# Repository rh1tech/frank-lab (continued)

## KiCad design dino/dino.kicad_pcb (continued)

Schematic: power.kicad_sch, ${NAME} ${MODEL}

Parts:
C41: 1u; C_0603_1608Metric
C42: 680u; CP_Radial_D8.0mm_P3.50mm
C43, C48: 10u; C_0603_1608Metric
C44, C46, C47: 100n; C_0603_1608Metric
C45: 150p; C_0603_1608Metric
C49: 220u; CP_Radial_D6.3mm_P2.50mm
D4: SS34; D_SMA
F1: 1.5A 24V; Fuse_1812_4532Metric
J8: DC-005-5A-2.0; BarrelJack_DC-005; PARTREV A0
JP2: Force On; SolderJumper-2_P1.3mm_Open_Pad1.0x1.5mm
L2: 22uH; Inductor_CDRH104RNP
Q2, Q3: AO3401A; SOT-23-3L_AOS
R33, R34, R35, R37, R39, R40: 100K; R_0603_1608Metric
R36: 10K; R_0603_1608Metric
R38: 39K; R_0603_1608Metric
R41: 8.2K; R_0603_1608Metric
R42: 43K; R_0603_1608Metric
S5: SK12D07VG3NS; Switch_Slide_SK12D07VG3NS
TP2: +5V_DC; TestPoint_Pad_1.0x1.0mm
TP3: +5V_SEL; TestPoint_Pad_1.0x1.0mm
U12: MP1584EN-LF-Z; SOIC-9_P1.27mm; Mouser Part Number 946-MP1584ENLFZ

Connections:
+5V_DC: C47.2, C48.1, C49.1, L2.2, R42.1, TP2.1 (1_1); also elsewhere on the board
+5V_SEL: C41.1, Q3.2 (S), R33.1, TP3.1 (1_1); also elsewhere on the board
GND: C42.2, C43.2, C44.2, C47.1, C48.2, C49.2, D4.2 (A), J8.2, JP2.1 (A), R34.2, R38.2, R39.2, R40.2, R41.1, S5.2, U12.5 (GND), U12.9 (EP); also elsewhere on the board
unnamed: C45.2, R39.1
unnamed: C46.2, D4.1 (K), L2.1, U12.1 (SW)
unnamed: F1.1, J8.1
unnamed: JP2.2 (B), R36.2, S5.3
unnamed: F1.2, Q2.3 (D)
unnamed: Q2.1 (G), R34.1, R35.1
unnamed: C42.1, C43.1, C44.1, Q2.2 (S), R35.2, R37.2, U12.7 (VIN)
unnamed: C41.2, Q3.1 (G), R33.2, R36.1
unnamed: C46.1, U12.8 (BST)
unnamed: C45.1, U12.3 (COMP)
unnamed: R37.1, R38.1, U12.2 (EN)
unnamed: R41.2, R42.2, U12.4 (FB)
unnamed: R40.1, U12.6 (FREQ)
VBUS: Q3.3 (D); also elsewhere on the board

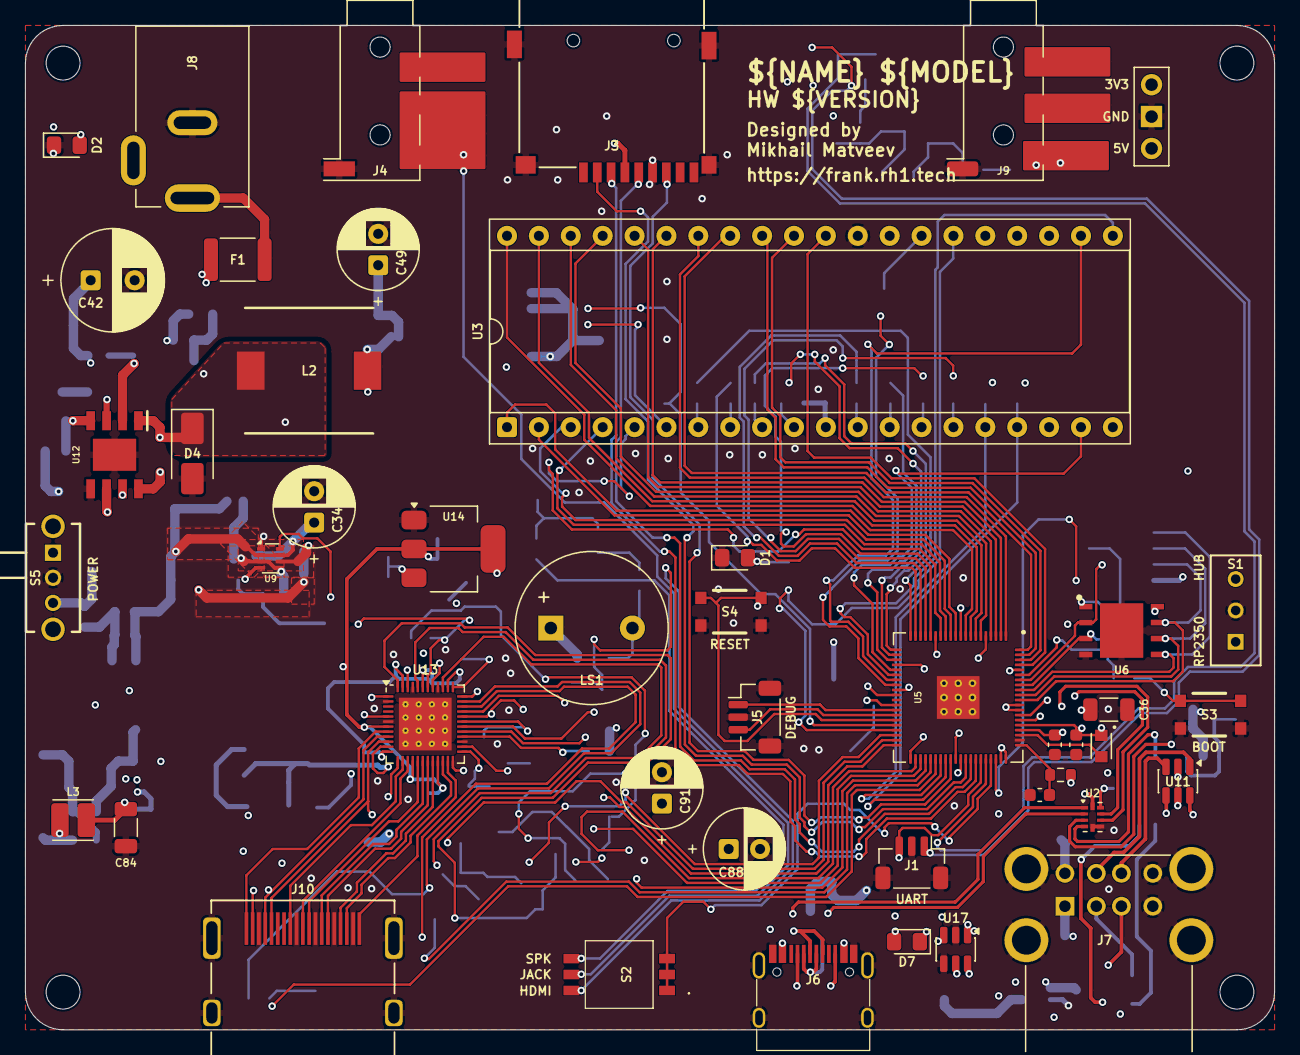
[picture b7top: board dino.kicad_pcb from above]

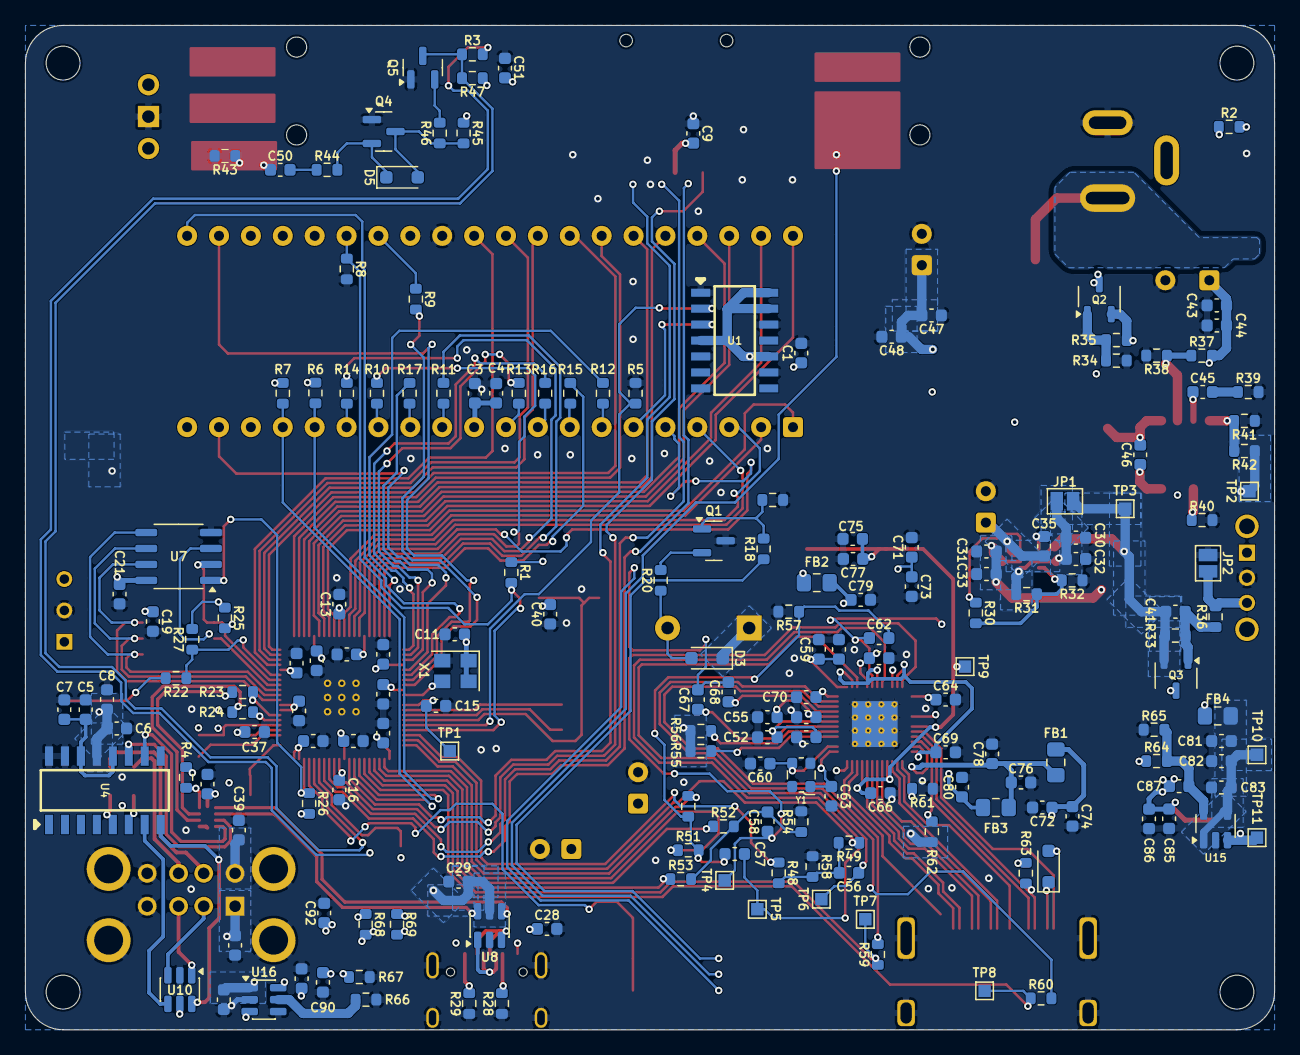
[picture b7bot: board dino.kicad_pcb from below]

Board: 4 copper layers, 99.5 x 80.0 mm, 234 parts (185 on the bottom side), 174 nets.

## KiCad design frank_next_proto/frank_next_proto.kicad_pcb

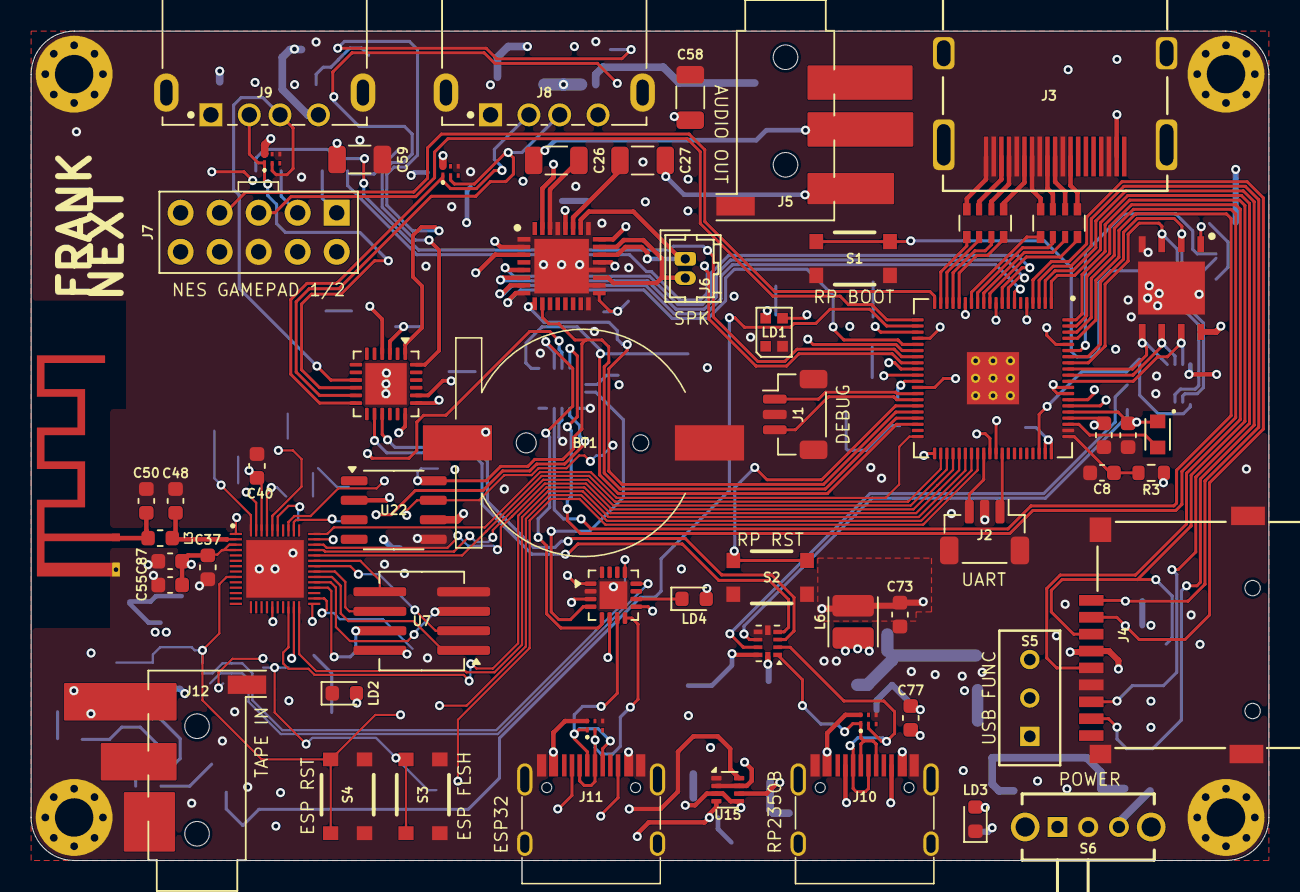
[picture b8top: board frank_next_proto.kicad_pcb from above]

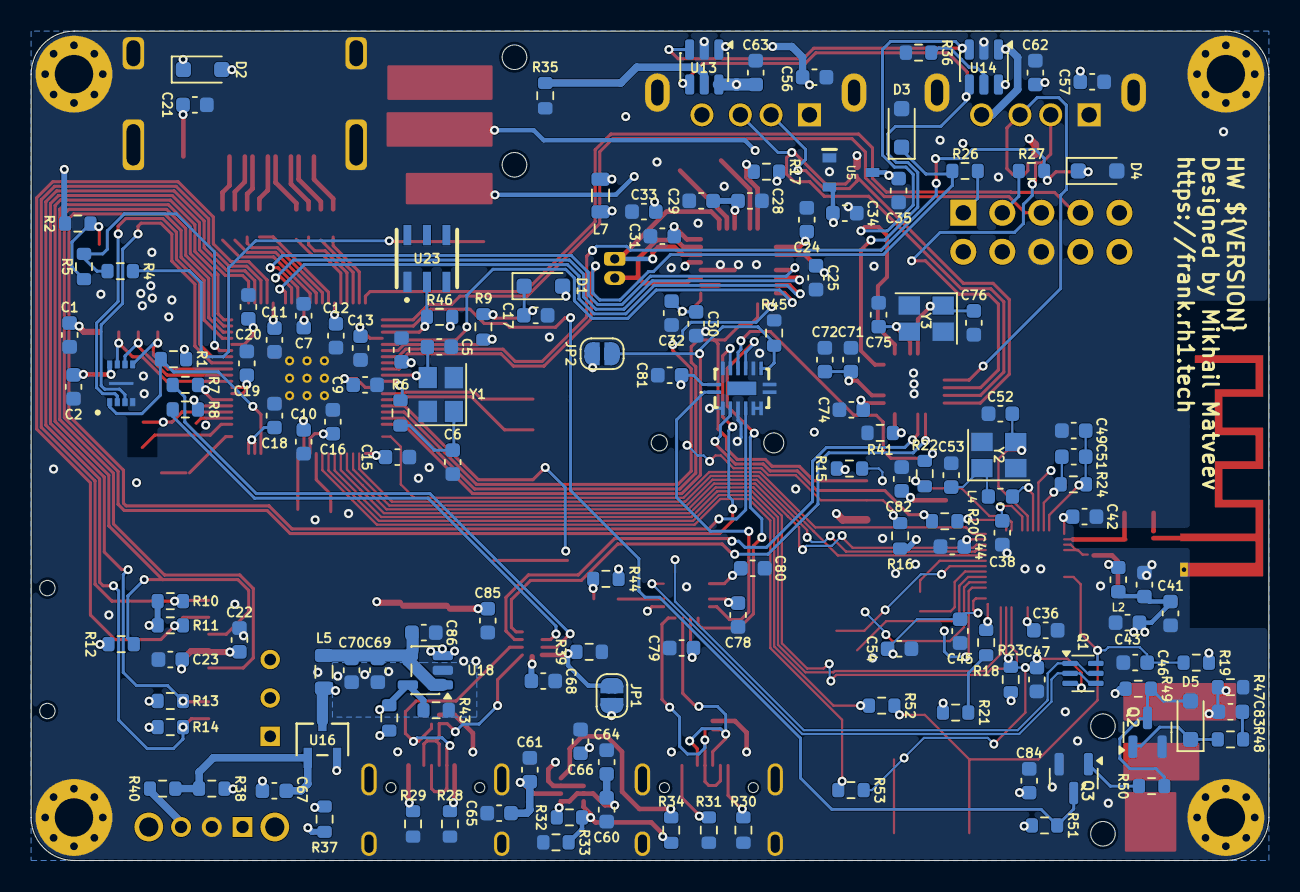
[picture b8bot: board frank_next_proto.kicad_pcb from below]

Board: 4 copper layers, 80.6 x 54.0 mm, 211 parts (148 on the bottom side), 160 nets.

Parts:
AE1: Antenna; Antenna_2.4GHz
BT1: CR1220; Battery_CR1220
C1, C2, C7, C10, C11, C12, C13, C14, C15, C16, C17, C18, C19, C20, C21, C23, C24, C25, C29, C32, C33, C37, C39, C40, C42, C44, C45, C56, C57, C60, C61, C67, C68, C78, C79, C80, C81, C82, C83, C84, C86: 100nF; C_0603_1608Metric
C3, C4, C8, C9: 4.7uF; C_0603_1608Metric
C5, C6: 15pF; C_0603_1608Metric
C22, C28, C30, C31, C41, C55, C62, C63, C64, C65, C66, C69, C70, C71, C73, C74, C85, C87: 10uF; C_0603_1608Metric
C26, C27, C58, C59: 100uF; C_1206_3216Metric
C34, C35, C36, C43, C46, C54, C72: 1uF; C_0603_1608Metric
C38: 100pF; C_0603_1608Metric
C47: 1nF; C_0603_1608Metric
C48: 1.5pF; C_0603_1608Metric
C49: 10nF; C_0603_1608Metric
C50: 2.4pF; C_0603_1608Metric
C51: 3.3nF; C_0603_1608Metric
C52, C53, C75, C76: 12pF; C_0603_1608Metric
C77: 22pF; C_0603_1608Metric
D1, D2: 1N5819WS; D_SOD-323
D3, D4: 3V3; D_SOD-323
D5: 1N4148; D_SOD-323
H1, H2, H3, H4: MountingHole; MountingHole_2.5mm_Pad_Via
J1: Debug; JST_SH_1x03_P1.00mm_Vertical
J2: UART; JST_SH_1x03_P1.00mm_Vertical
J3: DC3RX19JA2; HDMI_Female
J4: 104031-0811; MicroSD_SMD_Long
J5: PJ-320D; AudioJack_3.5mm_PJ320D_AudioOut
J6: Speaker; JST_GH_1x02_P1.25mm
J7: NES Gamepad 1/2; PinHeader_2x05_P2.54mm_Vertical
J8, J9: 676430910; USB_A_Short
J10, J11: USB4215-03-A; USB_C_Receptacle
J12: PJ-320D; AudioJack_3.5mm_PJ320D_TapeIn
JP1: USB Debug; SolderJumper-2_P1.3mm_Open_RoundedPad1.0x1.5mm
JP2: ESP Debug; SolderJumper-2_P1.3mm_Open_RoundedPad1.0x1.5mm
L1: 3.3µH; L_Murata_LQH2MCN_2.0x1.6mm
L2: 2nH; L_0603_1608Metric
L3: 2.7nH/0R; L_0603_1608Metric
L4: 24nH/0R; L_0603_1608Metric
L5, L7: 330R 2A; L_0805_2012Metric
L6: 2.2uH; L_Cenker_CKCS3015
LD1: WS2812B-2020; LED_WS2812B-2020_PLCC4_2.0x2.0mm
LD2: Blue; LED_0603_1608Metric
LD3: Green; LED_0603_1608Metric
LD4: Orange; LED_0603_1608Metric
Q1: UMH3N; SOT-363
Q2, Q3: BC850; SOT-23
R1, R2, R10, R11, R12, R13, R14, R17, R19, R23, R39, R45, R48, R49, R50: 10K; R_0603_1608Metric
R3: 33R; R_0603_1608Metric
R4, R6, R26, R27, R37, R40, R44, R51, R52, R53: 1K; R_0603_1608Metric
R5, R18: 0R; R_0603_1608Metric
R7, R8: 27R; R_0603_1608Metric
R9, R20, R22: 330R; R_0603_1608Metric
R15, R16, R41, R46: 4.7K; R_0603_1608Metric
R21: 220R; R_0603_1608Metric
R24: 20K; R_0603_1608Metric
R28, R29, R30, R31: 5.1K; R_0603_1608Metric
R32: 300K; R_0603_1608Metric
R33, R35, R36, R38, R42: 100K; R_0603_1608Metric
R34: 1M; R_0603_1608Metric
R43: 22K; R_0603_1608Metric
R47: 100R; R_0603_1608Metric
RN1, RN2: 270R; R_Array_4x0603
S1: RP Boot; Button_SMD_3x4x2mm
S2: RP Reset; Button_SMD_3x4x2mm
S3: ESP Flash; Button_SMD_3x4x2mm
S4: ESP Reset; Button_SMD_3x4x2mm
S5: SS12D00; Switch_Slide_SS12D00
S6: SK12D07VG3NS; Switch_Slide_SK12D07VG3NS_PWR
U1: APS6404L-3SQR-ZR; PSON50P200X300X50-9N
U2: W25Q128JVPIQ; WSON-8-1EP_6x5mm_P1.27mm_EP3.45x4.35mm
U3: RP2350B; RP2350-QFN-80_10x10_P0.4mm
U4: TLV320DAC3100IRHBR
U5: XC6206P182MR-G
U6: ESP32-D0WD-V3; QFN-48-1EP_5x5mm_P0.35mm_EP3.75x3.75mm
U7: W25Q32JVSIQ; SOIC-8_Longer
U9, U10, U11, U12: TPD4S012DRYR
U13, U14: CH217K; SOT-23-6
U15: TPS2116DRL; SOT-583-8
U16: AO3401A; SOT-23-3L_AOS
U17: TS3USB221RSER; UQFN-10
U18: SY8089AAAC; SOT-23-5
U19: CH334F; QFN-24-1EP_4x4mm_P0.5mm_EP2.7x2.7mm
U20: CH343P; WCH_QFN-16-1EP_3x3mm_P0.5mm_EP1.8x1.8mm
U21: 74HC4052BQ; 74HC4052BQ115
U22: DS3231MZ; SO-8_3.9x4.9mm_P1.27mm
U23: DS2401P+; TSOC-6
Y1, Y3: 12 MHz; Crystal_SMD_3225-4Pin_3.2x2.5mm
Y2: 40 MHz; Crystal_SMD_3225-4Pin_3.2x2.5mm

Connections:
+1V1: C4.1, C7.1, C9.1, C10.1, L1.1, U3.10 (DVDD), U3.32 (DVDD), U3.51 (DVDD), U3.65 (VREG_FB)
+1V8: C25.2, C34.2, U4.3 (DVDD), U5.2 (VOUT)
+3.3VP: C37.1, C55.1, C87.1, L2.2, U6.3 (VDD3P3_1), U6.4 (VDD3P3_2)
+3V3: C1.1, C2.2, C3.1, C11.1, C12.1, C13.1, C14.1, C15.1, C16.1, C18.1, C19.1, C20.1, C22.2, C23.2, C24.1, C28.2, C29.2, C30.2, C32.2, C35.2, C36.1, C38.1, C39.1, C40.1, C41.1, C42.1, C43.1, C44.1, C68.2, C73.1, C77.1, C80.2, C81.2, C82.1, C84.2, C85.1, J4.4 (VDD), JP1.1 (A), JP2.1 (A), L2.1, L6.1, R1.2, R2.2, R3.1, R10.1, R11.1, R12.1, R13.1, R14.1, R15.2, R16.2, R17.2, R19.2, R23.2, R37.2, R42.1, R44.2, R46.1, R49.1, R51.1, S5.2, U1.8 (VDD), U2.8 (VCC), U3.5 (IOVDD), U3.15 (IOVDD), U3.24 (IOVDD), U3.29 (IOVDD), U3.41 (IOVDD), U3.50 (IOVDD), U3.59 (ADC_AVDD), U3.60 (IOVDD), U3.64 (VREG_VIN), U3.68 (USB_OTP_VDD), U3.69 (QSPI_IOVDD), U3.76 (IOVDD), U4.2 (IOVDD), U4.17 (AVDD), U4.28 (HPVDD), U5.3 (VIN), U6.1 (VDDA_1), U6.19 (VDD3P3_RTC), U6.37 (VDD3P3_CPU), U6.43 (VDDA_2), U6.46 (VDDA_3), U17.10 (VCC), U20.1 (VIO), U21.16 (VCC_1), U22.2 (VCC)
/Audio/+5V_SPK: C31.2, C33.2, L7.1, U4.21 (SPKVDD_1), U4.24 (SPKVDD_2)
/Audio/SPKM: J6.2, U4.19 (SPKM_1), U4.23 (SPKM_2)
/Audio/SPKP: J6.1, U4.22 (SPKP_1), U4.26 (SPKP_2)
/CH343P/DTR: Q1.2 (B1), Q1.4 (E2), U20.12 (~DTR)
/CH343P/RTS: Q1.1 (E1), Q1.5 (B2), U20.13 (~RTS)
/CH343P/RXD: U20.5 (RXD), U21.12 (1Y0)
/CH343P/TXD: U20.4 (TXD), U21.1 (2Y0)
/CS (GPIO33/GPIO5): U3.42 (GPIO33), U6.34 (GPIO5)
/D+: R7.1, U17.8 (D+)
/D-: R8.1, U17.7 (D-)
/ESP32/ANT: AE1.1 (A), C50.1, L3.1
/ESP32/CAP1: C49.1, C51.1, R24.2, U6.48 (CAP1)
/ESP32/CAP2: C51.2, R24.1, U6.47 (CAP2)
/ESP32/GPIO16: R18.2, R21.2
/ESP32/LNA_IN: C48.1, L3.2, U6.2 (LNA_IN)
/ESP32/SCK/CLK: U6.31 (SD_CLK), U7.6 (CLK)
/ESP32/SCS/CMD: U6.30 (SD_CMD), U7.1 (~CS)
/ESP32/SDI/SD1: U6.33 (SD_DATA_1), U7.5 (DI(IO0))
/ESP32/SDO/SD0: U6.32 (SD_DATA_0), U7.2 (DO(IO1))
/ESP32/SHD/SD2: U6.28 (SD_DATA_2), U7.7 (IO3)
/ESP32/SWP/SD3: U6.29 (SD_DATA_3), U7.3 (IO2)
/ESP32/U0RXD: R20.2, U6.40 (U0RXD)
/ESP32/U0TXD: R22.2, U6.41 (U0TXD)
/ESP32/VDD_SDIO: C45.2, C54.1, U6.26 (VDD_SDIO), U7.8 (VCC)
/ESP32/XTAL_N: C52.1, U6.44 (XTAL_N), Y2.3
/ESP32/XTAL_P: L4.1, U6.45 (XTAL_P)
/ESP Multiplexer/1Z: R22.1, U21.13 (1Z)
/ESP Multiplexer/2Z: R20.1, U21.3 (2Z)
/GPIO0/RXD: U3.77 (GPIO0), U21.5 (2Y1)
/GPIO1/TXD: U3.78 (GPIO1), U21.14 (1Y1)
/GPIO2/CLK: J4.5 (CLK), U3.79 (GPIO2)
/GPIO3/CMD: J4.3 (CMD), R12.2, U3.80 (GPIO3)
/GPIO4/DAT0: J4.7 (DAT0), R13.2, U3.1 (GPIO4)
/GPIO5/DAT1: J4.8 (DAT1), R14.2, U3.2 (GPIO5)
/GPIO6/DAT2: J4.1 (DAT2), R10.2, U3.3 (GPIO6)
/GPIO7/DAT3: J4.2 (DAT3/CD), R11.2, U3.4 (GPIO7)
/GPIO9/BCLK: U3.7 (GPIO9), U4.7 (BCLK)
/GPIO10/WCLK: U3.8 (GPIO10), U4.6 (WCLK)
/GPIO11/DIN: U3.9 (GPIO11), U4.5 (DIN)
/GPIO12/CLKN: RN1.4 (R4.1), U3.11 (GPIO12)
/GPIO13/CLKP: RN1.3 (R3.1), U3.12 (GPIO13)
/GPIO14/D0N: RN1.2 (R2.1), U3.13 (GPIO14)
/GPIO15/D0P: RN1.1 (R1.1), U3.14 (GPIO15)
/GPIO16/D1N: RN2.4 (R4.1), U3.16 (GPIO16)
/GPIO17/D1P: RN2.3 (R3.1), U3.17 (GPIO17)
/GPIO18/D2N: RN2.2 (R2.1), U3.18 (GPIO18)
/GPIO19/D2P: RN2.1 (R1.1), U3.19 (GPIO19)
/GPIO20: J7.4, U3.20 (GPIO20)
/GPIO21: J7.3, U3.21 (GPIO21)
/GPIO22/LOAD_IN: Q3.3 (C), R51.2, U3.22 (GPIO22)
/GPIO23/DATA: R46.2, U3.23 (GPIO23), U23.2 (DATA)
/GPIO24/MCLK: U3.25 (GPIO24), U4.8 (MCLK)
/GPIO26: D4.1 (K), R27.1, U3.27 (GPIO26)
/GPIO27: D3.1 (K), R26.1, U3.28 (GPIO27)
/GPIO28/SDA: R16.1, U3.36 (GPIO28), U4.9 (SDA), U22.7 (SDA)
/GPIO29/SCL: R15.1, U3.37 (GPIO29), U4.10 (SCL), U22.8 (SCL)
/GPIO30/S0: JP2.2 (B), R45.1, U3.38 (GPIO30), U21.10 (S0)
/GPIO38/CHIP_PU: C46.1, Q1.6 (C1), R19.1, R52.2, S4.1, S4.3, U6.9 (CHIP_PU)
/GPIO39/GPIO0: C47.1, Q1.3 (C2), R23.1, R53.2, S3.1, S3.3, U6.23 (GPIO0)
/HS (GPIO36/GPIO2): U3.45 (GPIO36), U6.22 (GPIO2)
/MISO (GPIO32/GPIO19): U3.40 (GPIO32), U6.38 (GPIO19)
/MOSI (GPIO35/GPIO23): U3.44 (GPIO35), U6.36 (GPIO23)
/NES Gamepad/G_DATA1: J7.2, R27.2
/NES Gamepad/G_DATA2: J7.1, R26.2
/READY (GPIO37/GPIO4): U3.46 (GPIO37), U6.24 (GPIO4)
/RP2350B/BOOT: R4.2, S1.1, S1.3
/RP2350B/GPIO40/UART_1: J2.1, U3.49 (GPIO40_ADC0)
/RP2350B/GPIO41/UART_3: J2.3, U3.52 (GPIO41_ADC1)
/RP2350B/GPIO47: R1.1, U1.1 (~CE), U3.58 (GPIO47_ADC7)
/RP2350B/QSPI_SCLK: U1.6 (SCLK), U2.6 (CLK), U3.71 (QSPI_SCLK)
/RP2350B/QSPI_SD0: U1.5 (SI/SIO(0)), U2.5 (DI_(IO0)), U3.72 (QSPI_SD0)
/RP2350B/QSPI_SD1: U1.2 (SO/SIO(1)), U2.2 (DO_(IO1)), U3.74 (QSPI_SD1)
/RP2350B/QSPI_SD2: U1.3 (SIO(2)), U2.3 (~WP_(IO2)), U3.73 (QSPI_SD2)
/RP2350B/QSPI_SD3: U1.7 (SIO(3)), U2.7 (~HOLD_OR_/RESET_(IO3)), U3.70 (QSPI_SD3)
/RP2350B/QSPI_SS: R4.1, R5.1, U3.75 (QSPI_SS)
/RP2350B/RUN: S2.1, S2.3, U3.35 (RUN)
/RP2350B/SWCLK: J1.3, U3.33 (SWCLK)
/RP2350B/SWD: J1.1, U3.34 (SWD)
/RP2350B/VREG_AVDD: C8.1, R3.2, U3.61 (VREG_AVDD)
/RP2350B/VREG_LX: L1.2, U3.63 (VREG_LX)
/RP2350B/XIN: C5.1, U3.30 (XIN), Y1.3
/RP2350B/XOUT: R6.2, U3.31 (XOUT)
/SCK (GPIO34/GPIO18): U3.43 (GPIO34), U6.35 (GPIO18)
/Tape In/TAPE: C83.1, J12.T, R47.1
/UD+: J11.6 (DP1), J11.8 (DP2), U12.1 (D+), U20.7 (UD+)
/UD-: J11.5 (DN2), J11.7 (DN1), U12.2 (D-_), U20.8 (UD-)
/USB/+5V_BUCK: C69.1, C70.1, C86.1, L5.2, U18.1 (EN), U18.4 (IN)
/USB/D2+: J10.6 (DP1), J10.8 (DP2), U11.1 (D+), U17.1 (1D+)
/USB/D2-: J10.5 (DN2), J10.7 (DN1), U11.2 (D-_), U17.2 (1D-)
/USB/DH+: U17.3 (2D+), U19.15 (DPU+)
/USB/DH-: U17.4 (2D-), U19.14 (DMU-)
/USB/DS1+: J8.3 (D+), U9.1 (D+), U19.12 (DP1+)
/USB/DS1-: J8.2 (D-), U9.2 (D-_), U19.11 (DM1-)
/USB/DS2+: J9.3 (D+), U10.1 (D+), U19.10 (DP2+)
/USB/DS2-: J9.2 (D-), U10.2 (D-_), U19.9 (DM2-)
/USB/OVCUR: U13.3 (FLAG#), U14.3 (FLAG#), U19.1 (~OVCUR)
/USB/PWREN: U13.4 (EN#), U14.4 (EN#), U19.24 (~PWREN)
/USB/S: JP1.2 (B), R39.2, S5.3, U17.9 (S)
/USB/ST: R34.2, U15.8 (ST)
/USB/VBUS_IN: C66.1, C67.2, R38.2, U15.2 (VOUT), U15.7 (VOUT), U16.2 (S)
/USB/VBUS_IN1: C60.2, C64.2, J11.2 (VBUS), J11.11 (VBUS), R32.2, U12.6 (VBUS), U15.3 (VIN1), U15.5 (MODE)
/USB/VBUS_IN2: C61.2, C65.2, J10.2 (VBUS), J10.11 (VBUS), U11.6 (VBUS), U15.6 (VIN2)
/USB/VBUS_P1: C56.1, C58.1, J8.1 (VBUS), U9.6 (VBUS), U13.1 (VOUT)
/USB/VBUS_P2: C57.1, C59.1, J9.1 (VBUS), U10.6 (VBUS), U14.1 (VOUT)
/USB/VDD33: C71.2, C72.2, U19.20 (VDD33_{LDO})
/USB/XTAL_N: C75.1, U19.3 (XO), Y3.3
/USB/XTAL_P: C76.1, U19.4 (XI), Y3.1
GND: AE1.2 (Shield), BT1.2 (-), C1.2, C2.1, C3.2, C4.2, C5.2, C6.2, C7.2, C8.2, C9.2, C10.2, C11.2, C12.2, C13.2, C14.2, C15.2, C16.2, C17.2, C18.2, C19.2, C20.2, C21.2, C22.1, C23.1, C24.2, C25.1, C28.1, C29.1, C30.1, C31.1, C32.1, C33.1, C34.1, C35.1, C36.2, C37.2, C38.2, C39.2, C40.2, C41.2, C42.2, C43.2, C44.2, C45.1, C46.2, C47.2, C48.2, C49.2, C50.2, C52.2, C53.2, C54.2, C55.2, C56.2, C57.2, C58.2, C59.2, C60.1, C61.1, C62.1, C63.1, C64.1, C65.1, C66.2, C68.1, C69.2, C70.2, C71.1, C72.1, C73.2, C74.1, C75.2, C76.2, C78.1, C79.1, C80.1, C81.1, C82.2, C84.1, C85.2, C86.2, C87.2, D3.2 (A), D4.2 (A), H1.1 (1_1), H2.1 (1_1), H3.1 (1_1), H4.1 (1_1), J1.2, J2.2, J3.2 (G_D2), J3.5 (G_D1), J3.8 (G_D0), J3.11 (G_CLK), J3.17 (G_DDC/CEC), J3.20 (SHIELD1), J3.21 (SHIELD2), J3.22 (SHIELD3), J3.23 (SHIELD4), J4.6 (VSS), J4.SH (SHIELD), J5.S, J7.8, J8.4 (GND), J8.5 (Shield), J9.4 (GND), J9.5 (Shield), J10.1 (GND), J10.12 (GND), J10.13 (SHIELD), J11.1 (GND), J11.12 (GND), J11.13 (SHIELD), J12.S, LD1.2 (VSS), LD2.1 (K), LD3.1 (K), Q2.2 (E), Q3.2 (E), R28.1, R29.1, R30.1, R31.1, R33.1, R35.1, R36.1, R39.1, R41.2, R43.2, R45.2, R47.2, S1.2, S1.4, S2.2, S2.4, S3.2, S3.4, S4.2, S4.4, S6.2, U1.4 (VSS), U1.9 (EXP), U2.4 (GND_1), U2.9 (GND_2), U3.62 (VREG_PGND), U3.81 (GND), U4.1 (IOVSS), U4.16 (AVSS), U4.18 (DVSS), U4.20 (SPKVSS_1), U4.25 (SPKVSS_2), U4.29 (HPVSS), U4.33 (EP), U5.1 (VSS), U6.49 (GND), U7.4 (GND), U9.4 (GND), U10.4 (GND), U11.4 (GND), U12.4 (GND), U13.2 (GND), U14.2 (GND), U15.1 (GND), U17.5 (GND), U17.6 (~OE), U18.2 (GND), U19.25 (GND), U20.2 (GND), U20.17 (GND_EPAD), U21.2 (2Y2), U21.4 (2Y3), U21.6 (~E), U21.7 (VEE), U21.8 (GND), U21.9 (S1), U21.11 (1Y3), U21.15 (1Y2), U22.5 (GND), U23.1 (GND), Y1.2, Y1.4, Y2.2, Y2.4, Y3.2, Y3.4
unnamed: BT1.1 (+), U22.6 (VBAT)
unnamed: C6.1, R6.1, Y1.1
unnamed: C26.1, J5.R
unnamed: C27.1, J5.T
unnamed: C53.1, L4.2, Y2.1
unnamed: C83.2, R48.1
unnamed: C17.1, D1.1 (K), LD1.4 (VDD)
unnamed: C21.1, D2.1 (K), J3.18 (+5V)
unnamed: D5.2 (A), Q2.3 (C), R49.2, R50.1
unnamed: D5.1 (K), Q2.1 (B), R48.2
unnamed: J3.12 (CLKN), RN1.5 (R4.2)
unnamed: J3.10 (CLKP), RN1.6 (R3.2)
unnamed: J3.9 (D0N), RN1.7 (R2.2)
unnamed: J3.7 (D0P), RN1.8 (R1.2)
unnamed: J3.6 (D1N), RN2.5 (R4.2)
unnamed: J3.4 (D1P), RN2.6 (R3.2)
unnamed: J3.3 (D2N), RN2.7 (R2.2)
unnamed: J3.1 (D2P), RN2.8 (R1.2)
unnamed: J10.4 (CC1), R28.2
unnamed: J10.10 (CC2), R29.2
unnamed: J11.4 (CC1), R30.2
unnamed: J11.10 (CC2), R31.2
unnamed: LD1.3 (DIN), R9.1
unnamed: LD2.2 (A), R21.1
unnamed: LD3.2 (A), R37.1
unnamed: LD4.2 (A), R44.1
unnamed: LD4.1 (K), U20.10 (~ACT)
unnamed: Q3.1 (B), R50.2
unnamed: R40.2, S6.3
unnamed: R2.1, R5.2, U2.1 (~CS)
unnamed: R9.2, U3.26 (GPIO25)
unnamed: R52.1, U3.47 (GPIO38)
unnamed: R53.1, U3.48 (GPIO39)
unnamed: R8.2, U3.66 (USB_DM)
unnamed: R7.2, U3.67 (USB_DP)
unnamed: C27.2, U4.27 (HPL)
unnamed: C26.2, U4.30 (HPR)
unnamed: R17.1, U4.31 (~RESET)
unnamed: R18.1, U6.25 (GPIO16)
unnamed: R35.2, U13.5 (ISET)
unnamed: R36.2, U14.5 (ISET)
unnamed: R32.1, R33.2, R34.1, U15.4 (PR1)
unnamed: C67.1, R38.1, R40.1, U16.1 (G)
unnamed: C77.2, R42.2, R43.1, U18.5 (FB)
unnamed: L6.2, U18.3 (LX)
unnamed: R41.1, U19.18 (PSELF)
unnamed: C79.2, U20.6 (V3_{OUT})
VBUS: C62.2, C63.2, C74.2, C78.2, D1.2 (A), D2.2 (A), J7.6, L5.1, L7.2, U13.6 (VIN), U14.6 (VIN), U16.3 (D), U19.19 (V5), U20.3 (VDD5), U20.9 (VBUS)

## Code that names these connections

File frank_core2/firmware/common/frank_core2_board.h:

/*
 * FRANK Core 2 — dual-RP2350 test firmware
 *
 * Copyright (c) 2026 Mikhail Matveev <xtreme@rh1.tech>
 * https://github.com/rh1tech/frank
 * SPDX-License-Identifier: GPL-3.0-or-later
 */

/*
 * frank_core2_board.h — GPIO map for the FRANK Core 2 board.
 *
 * Every assignment below was extracted from the KiCad netlist
 * (frank_core2.kicad_sch -> kicad-cli sch export netlist), so this file
 * is the single source of truth shared by the master and slave builds.
 *
 * U3 = RP2350B (master, QFN-80)   U6 = RP2350  (slave, QFN-60)
 *
 * The master carries all the user-facing peripherals: HDMI (J5), microSD
 * (J7), TDA1387 I2S DAC (U8), USB-C host/device (J8), WS2812B status LED
 * (LD1) and 8 MB PSRAM (U2) + 16 MB flash (U1).
 *
 * The slave carries its own 8 MB PSRAM (U5) + 16 MB flash (U4), a USB-C
 * port (J9), a blue status LED (LD2) and a UART header (J4). Everything
 * else it needs it gets over the inter-processor link.
 */
#ifndef FRANK_CORE2_BOARD_H
#define FRANK_CORE2_BOARD_H

/* =====================================================================
 * Inter-processor link
 *
 * Two independent 8-bit source-synchronous buses, each with its own
 * clock and VALID strobe, plus three single-wire control signals.
 *
 *   Bus A  master -> slave   M.GPIO20..27 -> S.GPIO1..8
 *                            M.GPIO28 (CLK, 33R R1) -> S.GPIO9
 *                            M.GPIO29 (VALID)       -> S.GPIO10
 *
 *   Bus B  slave -> master   S.GPIO11..18 -> M.GPIO30..37
 *                            S.GPIO19 (CLK, 33R R2) -> M.GPIO38
 *                            S.GPIO20 (VALID)       -> M.GPIO39
 *
 * Both buses share the same relative layout, which the PIO programs
 * rely on: CLK == DATA_BASE + 8, VALID == DATA_BASE + 9. That lets one
 * pair of PIO programs serve both directions on both chips with nothing
 * but a different pin base.
 *
 * Control signals (plain SIO, no PIO):
 *   FS      M.GPIO40 -> S.GPIO21   frame-sync / phase strobe (master out)
 *   DB_MS   M.GPIO41 -> S.GPIO22   doorbell, master -> slave
 *   DB_SM   M.GPIO42 <- S.GPIO23   doorbell, slave  -> master
 *
 * NOTE ON GPIO43: the schematic labels M.GPIO43 as "RUNA/SR" (slave
 * reset), but the net only reaches a 10K pull-up to +3V3 (R3) — it is
 * NOT wired to the slave's RUN pin (U6.26), which only sees reset
 * button S4. The firmware therefore cannot reset the slave in hardware;
 * both MCUs must be reset/flashed independently. See README.md.
 * ===================================================================== */

/* ---- Master side (RP2350B / U3) ---- */
#define M_LINK_A_DATA_BASE   20   /* GPIO20..27, master -> slave  */
#define M_LINK_A_CLK         28   /* == DATA_BASE + 8             */
#define M_LINK_A_VALID       29   /* == DATA_BASE + 9             */

#define M_LINK_B_DATA_BASE   30   /* GPIO30..37, slave -> master  */
#define M_LINK_B_CLK         38
#define M_LINK_B_VALID       39

#define M_LINK_FS            40   /* out */
#define M_LINK_DB_OUT        41   /* DB_MS, out */
#define M_LINK_DB_IN         42   /* DB_SM, in  */
#define M_LINK_SLAVE_RUN     43   /* pull-up only — not connected, see above */

/* ---- Slave side (RP2350 / U6) ---- */
#define S_LINK_A_DATA_BASE    1   /* GPIO1..8, master -> slave (RX) */
#define S_LINK_A_CLK          9
#define S_LINK_A_VALID       10

#define S_LINK_B_DATA_BASE   11   /* GPIO11..18, slave -> master (TX) */
#define S_LINK_B_CLK         19
#define S_LINK_B_VALID       20

#define S_LINK_FS            21   /* in  */
#define S_LINK_DB_IN         22   /* DB_MS, in  */
#define S_LINK_DB_OUT        23   /* DB_SM, out */

/* =====================================================================
 * Master peripherals
 * ===================================================================== */

/* HDMI (J5) via HSTX — clock pair first, N before P, matches Murmulator 2 */
#define HDMI_BASE_PIN        12
#define HDMI_PIN_CLKN        12
#define HDMI_PIN_CLKP        13
#define HDMI_PIN_D0N         14
#define HDMI_PIN_D0P         15
#define HDMI_PIN_D1N         16
#define HDMI_PIN_D1P         17
#define HDMI_PIN_D2N         18
#define HDMI_PIN_D2P         19

/* microSD (J7) on SPI0 — SDIO pin names from the schematic in comments */
#define SDCARD_PIN_SPI0_MISO  4   /* SD DAT0    */
#define SDCARD_PIN_SPI0_CS    5   /* SD DAT3/CD */
#define SDCARD_PIN_SPI0_SCK   6   /* SD CLK     */
#define SDCARD_PIN_SPI0_MOSI  7   /* SD CMD     */

/* TDA1387T I2S DAC (U8) */
#define I2S_DATA_PIN          9   /* U8.3 DATA */
#define I2S_CLOCK_PIN_BASE   10   /* U8.1 SCLK = 10, U8.2 LRCK = 11 */

/* WS2812B status LED (LD1) via 330R R11 */
#define M_LED_WS2812_PIN     46

/* 8 MB PSRAM (U2 ESP-PSRAM64H) chip select */
#define M_PSRAM_CS_PIN       47

/* Debug UART header J2: pin1 = GPIO0 (TX), pin2 = GND, pin3 = GPIO1 (RX) */
#define M_UART_ID            uart0
#define M_UART_TX_PIN         0
#define M_UART_RX_PIN         1

/* Spare / unrouted master GPIOs (available for probing) */
#define M_SPARE_GPIO_LIST    { 2, 3, 8, 44, 45 }

/* =====================================================================
 * Slave peripherals
 * ===================================================================== */

/* 8 MB PSRAM (U5 ESP-PSRAM64H) chip select */
#define S_PSRAM_CS_PIN        0

/* Blue status LED (LD2) via 1K R19 — active high */
#define S_LED_PIN            26

/* Debug UART header J4: pin1 = GPIO24 (TX), pin2 = GND, pin3 = GPIO25 (RX) */
#define S_UART_ID            uart1
#define S_UART_TX_PIN        24
#define S_UART_RX_PIN        25

/* Spare / unrouted slave GPIOs */
#define S_SPARE_GPIO_LIST    { 27, 28, 29 }

/* =====================================================================
 * Memory devices (identical part numbers on both sides)
 * ===================================================================== */
#define FRANK_FLASH_PART     "W25Q128JVPIQ"
#define FRANK_FLASH_BYTES    (16u * 1024u * 1024u)
#define FRANK_PSRAM_PART     "ESP-PSRAM64H"
#define FRANK_PSRAM_BYTES    (8u * 1024u * 1024u)

/* XIP windows: CS0 = flash, CS1 = PSRAM (psram_init maps it there).
 *
 * The 0x14000000 aliases bypass the XIP cache entirely. That matters for
 * the PSRAM presence and size probes: through the cached window a write
 * followed by a read of the same address is answered out of the 8 KiB
 * cache, so a missing chip looks present and an address that aliases
 * back onto offset 0 looks like it does not. Throughput measurements
 * deliberately use the cached window, because that is how real code
 * reaches these devices. */
#define FRANK_XIP_FLASH_BASE         0x10000000u
#define FRANK_XIP_PSRAM_BASE         0x11000000u
#define FRANK_XIP_FLASH_NOCACHE_BASE 0x14000000u
#define FRANK_XIP_PSRAM_NOCACHE_BASE 0x15000000u

#endif /* FRANK_CORE2_BOARD_H */

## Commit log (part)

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2026-04-22 Initial commit: experimental boards from murmulator lab
2026-04-22 Add FRANK M2 v2.07 from murmulator dev branch
2026-04-23 FRANK M2 Updates
2026-04-23 FRANK M2 WIP
2026-04-23 FRANK HW 2.07
2026-04-23 FRANK M2 HW 2.07 Release
2026-04-23 Board updates
2026-04-28 FRANK Pro 1.01 HW Release
2026-04-28 Repo cleanup
2026-04-28 chore: remove tracked .DS_Store files
2026-05-01 Nyx WIP
2026-05-02 Nyx Release HW 2.00
2026-05-04 Nyx renamed
2026-05-04 Cleanup
2026-05-07 Lab updates
2026-05-12 docs: link to frank.rh1.tech in README
2026-05-14 Nyx updates
2026-05-15 xt8086 WIP
2026-05-15 xt8086 1.03
2026-05-19 FRANK Air WIP
2026-05-21 Complete boards cleanup
2026-05-25 FRANK_MEGA WIP
2026-05-26 FRANK MEGA WIP
2026-05-29 New boards WIP
2026-05-29 FRANK AIR 1.00
2026-05-30 FRANK MEGA (HW 1.00)
2026-05-30 Nyx HW 2.02 - moved to frank repo
2026-05-31 FRANK MEGA HW 1.00
2026-05-31 Protea board added
2026-05-31 Protea update
2026-06-01 Protea 2.00 WIP
2026-06-02 Protea updates
2026-06-04 docs: standardize naming (assembly.pdf, bom.html, schematics.pdf)
    Latest versions:
    - frank_mega: 1.01
    - frank_air: 1.01
    - protea: 2.00
2026-06-08 MiniFRANK WIP
2026-06-09 FRANK TurboSound WIP
2026-06-09 FRANK TurboSound Module HW 2.00
2026-06-15 Hecate updates
2026-06-15 Hecate 3.00
2026-06-28 Minor updates
2026-06-28 MiniFRANK moved to main repo
2026-06-28 refactor: move turbosound, megafrank, zerofrank and hecate to murmulator
    These KiCad projects graduate from frank-lab into the maintained frank
    (murmulator) repository:
    - frank_turbosound -> turbosound (child sheet -> turbosound_ay)
    - frank_mega -> megafrank
    - frank_zero -> zerofrank
    - hecate (USB-to-PS/2 bridge board)
